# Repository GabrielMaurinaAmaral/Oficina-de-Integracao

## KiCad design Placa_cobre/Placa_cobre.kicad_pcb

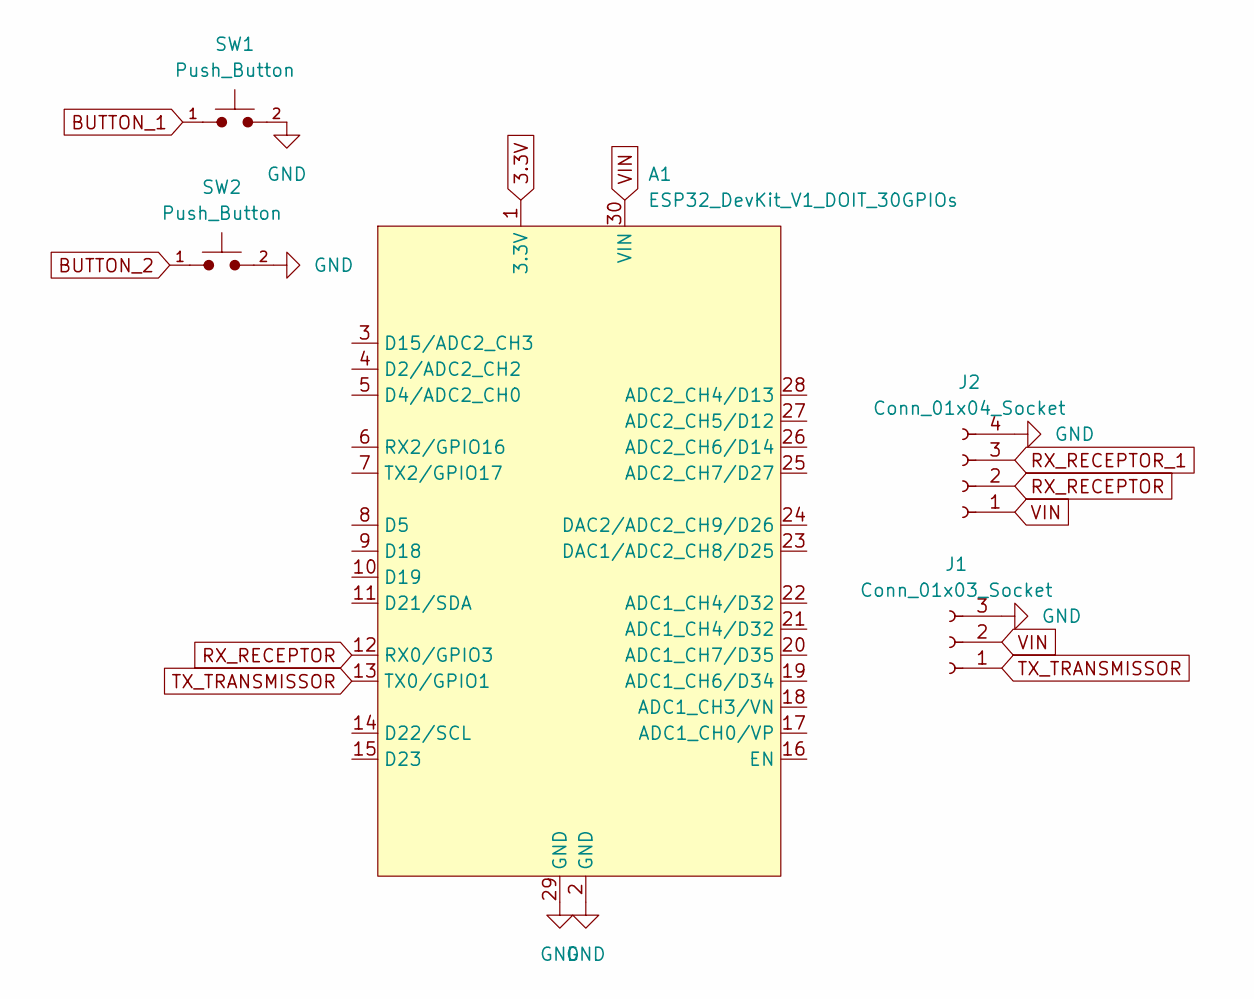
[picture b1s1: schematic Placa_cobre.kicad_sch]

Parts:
A1: ESP32_DevKit_V1_DOIT_30GPIOs; DOIT_ESP32_DEVKIT_30Pins
J1: Conn_01x03_Socket; PinSocket_1x03_P2.54mm_Vertical
J2: Conn_01x04_Socket; PinSocket_1x04_P2.54mm_Vertical
SW1, SW2: Push_Button; SW_PUSH_6mm

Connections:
3.3V: A1.1 (3.3V)
BUTTON_1: A1.17 (ADC1_CH0/VP), SW1.1
BUTTON_2: A1.15 (D23), SW2.1
GND: A1.2 (GND), A1.29 (GND), J1.3, J2.4, SW1.2, SW2.2
RX_RECEPTOR: A1.12 (RX0/GPIO3), J2.2
RX_RECEPTOR_1: J2.3
TX_TRANSMISSOR: A1.13 (TX0/GPIO1), J1.1
VIN: A1.30 (VIN), J1.2, J2.1

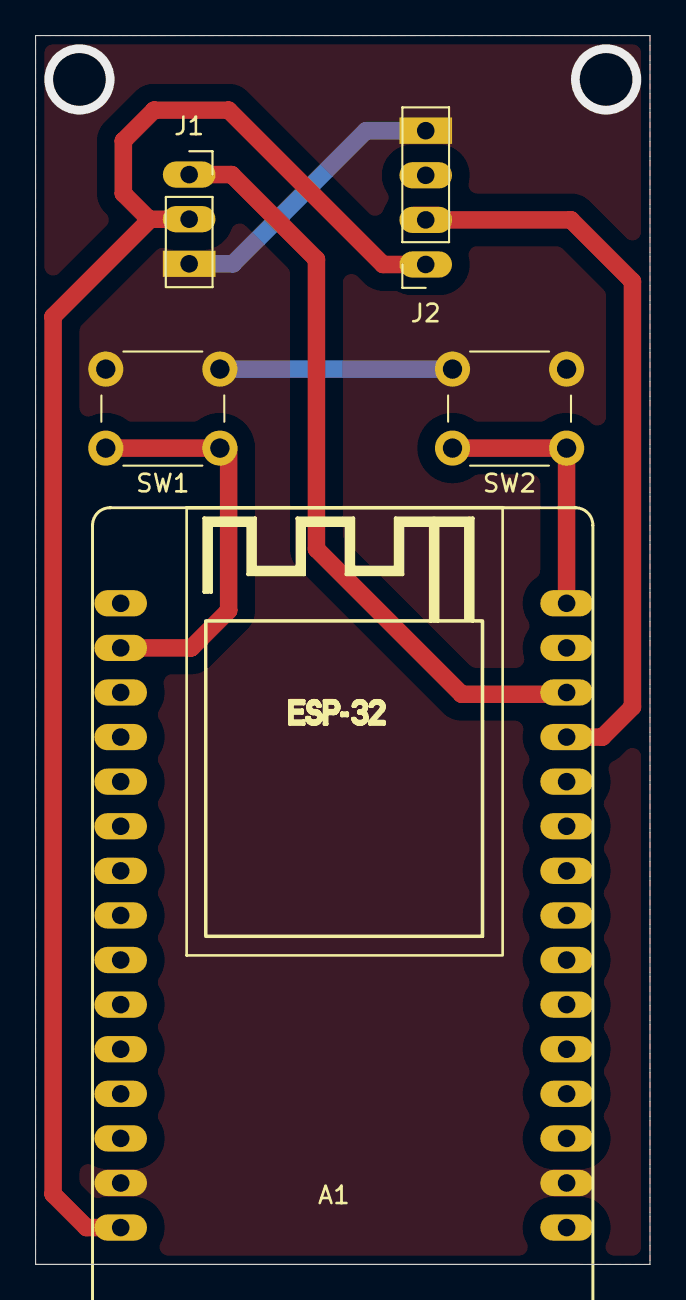
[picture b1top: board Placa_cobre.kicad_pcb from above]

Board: 2 copper layers, 35.0 x 70.0 mm, 5 parts (0 on the bottom side), 6 nets.

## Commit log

2024-12-28 primeiro commit com os codigos
2025-01-13 controle recebendo sinal tudo certo, transmissor mandando sinal quando aperta botao, e codigo organizados
2025-01-13 ajuste define BUTTON_PIN na main
2025-02-04 ajusto em transmissao
2025-02-10 codigo funcional, mandando e recebendo sinal, recpetor e transmissor
2025-02-20 tranasmissor mandado certo para o receptor
2025-02-24 codigo funconal
2025-02-24 porjeto final semi funcional
